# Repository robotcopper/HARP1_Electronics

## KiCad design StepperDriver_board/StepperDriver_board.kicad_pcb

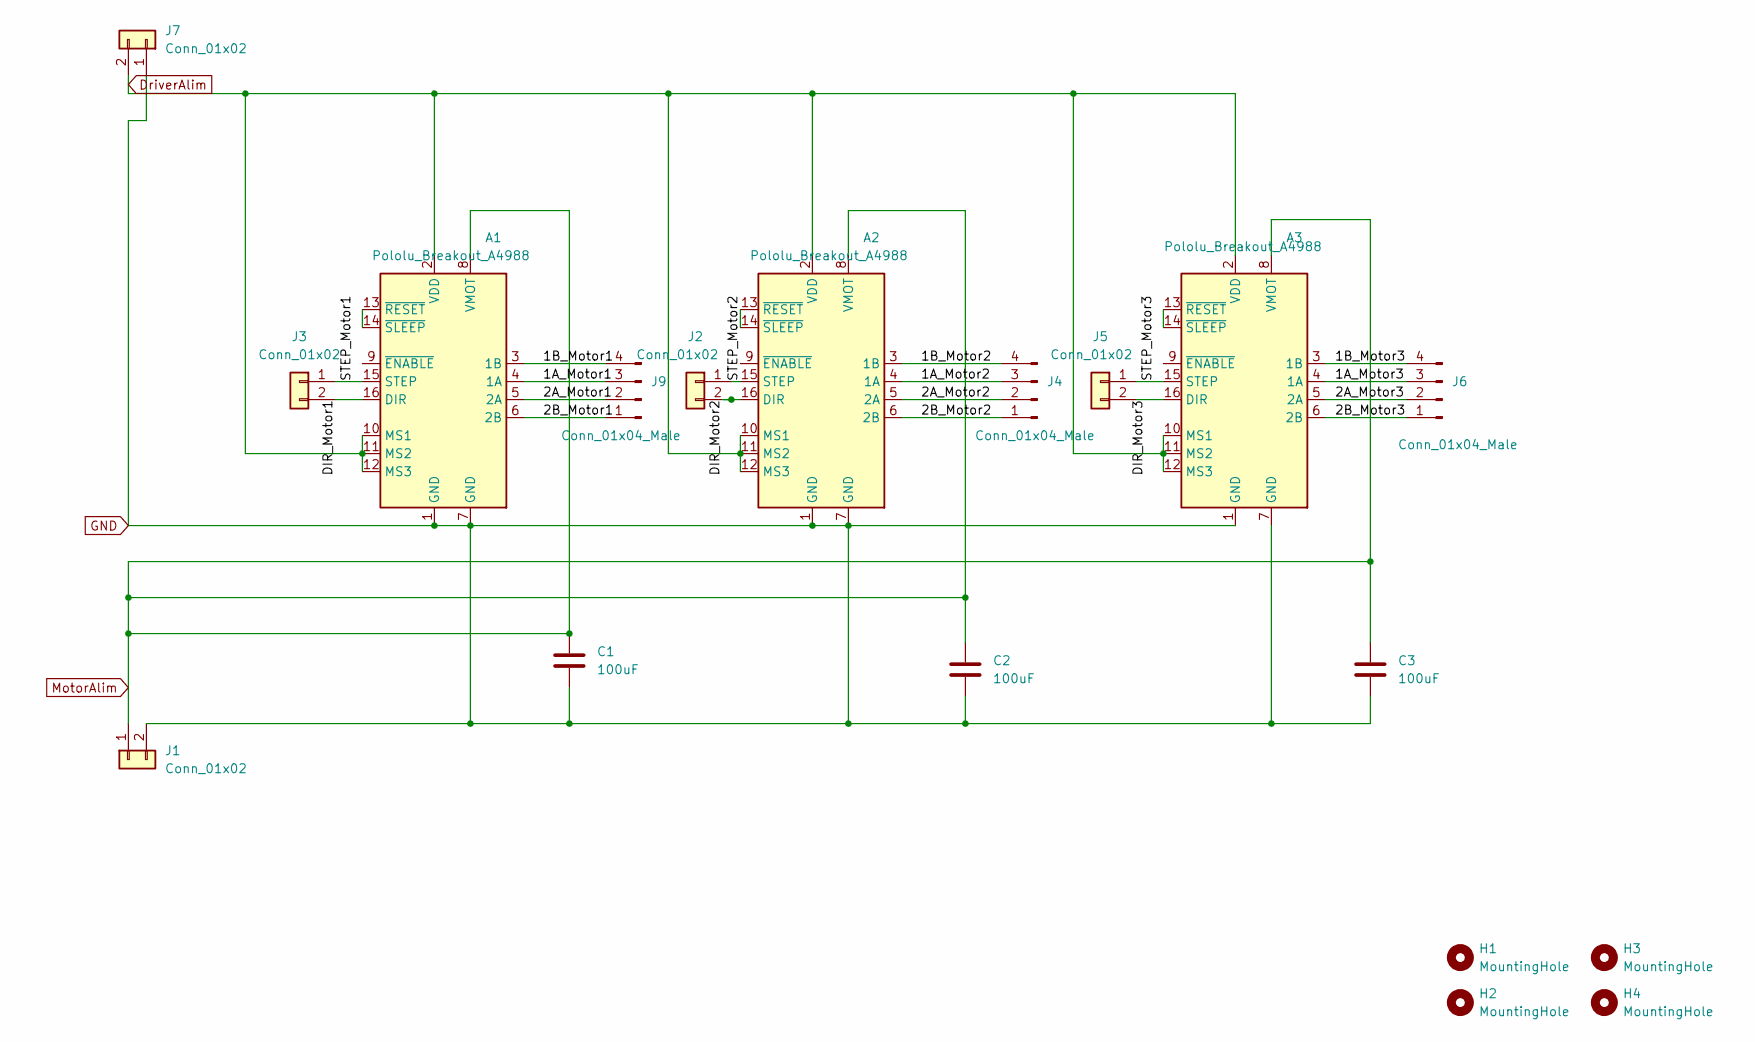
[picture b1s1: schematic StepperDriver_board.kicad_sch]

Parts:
A1, A2, A3: Pololu_Breakout_A4988; Pololu_Breakout-16_15.2x20.3mm
C1, C2, C3: 100uF; C_Radial_D8.0mm_H11.5mm_P3.50mm
H1, H2, H3, H4: MountingHole; MountingHole_3mm
J1, J2, J3, J5, J7: Conn_01x02; TerminalBlock_MetzConnect_Type073_RT02602HBLU_1x02_P5.08mm_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
J4, J6, J9: Conn_01x04_Male; PinHeader_1x04_P2.54mm_Vertical

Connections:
/1A_Motor1: A1.4 (1A), J9.3
/1A_Motor2: A2.4 (1A), J4.3
/1A_Motor3: A3.4 (1A), J6.3
/1B_Motor1: A1.3 (1B), J9.4
/1B_Motor2: A2.3 (1B), J4.4
/1B_Motor3: A3.3 (1B), J6.4
/2A_Motor1: A1.5 (2A), J9.2
/2A_Motor2: A2.5 (2A), J4.2
/2A_Motor3: A3.5 (2A), J6.2
/2B_Motor1: A1.6 (2B), J9.1
/2B_Motor2: A2.6 (2B), J4.1
/2B_Motor3: A3.6 (2B), J6.1
/DIR_Motor1: A1.16 (DIR), J3.2
/DIR_Motor2: A2.16 (DIR), J2.2
/DIR_Motor3: A3.16 (DIR), J5.2
/STEP_Motor1: A1.15 (STEP), J3.1
/STEP_Motor2: A2.15 (STEP), J2.1
/STEP_Motor3: A3.15 (STEP), J5.1
DriverAlim: A1.2 (VDD), A1.10 (MS1), A1.11 (MS2), A1.12 (MS3), A2.2 (VDD), A2.10 (MS1), A2.11 (MS2), A2.12 (MS3), A3.2 (VDD), A3.10 (MS1), A3.11 (MS2), A3.12 (MS3), J7.2
GND: A1.1 (GND), A1.7 (GND), A2.1 (GND), A2.7 (GND), A3.1 (GND), A3.7 (GND), C1.2, C2.2, C3.2, J1.2, J7.1
MotorAlim: A1.8 (VMOT), A2.8 (VMOT), A3.8 (VMOT), C1.1, C2.1, C3.1, J1.1
unnamed: A1.13 (~RESET), A1.14 (~SLEEP)
unnamed: A2.13 (~RESET), A2.14 (~SLEEP)
unnamed: A3.13 (~RESET), A3.14 (~SLEEP)

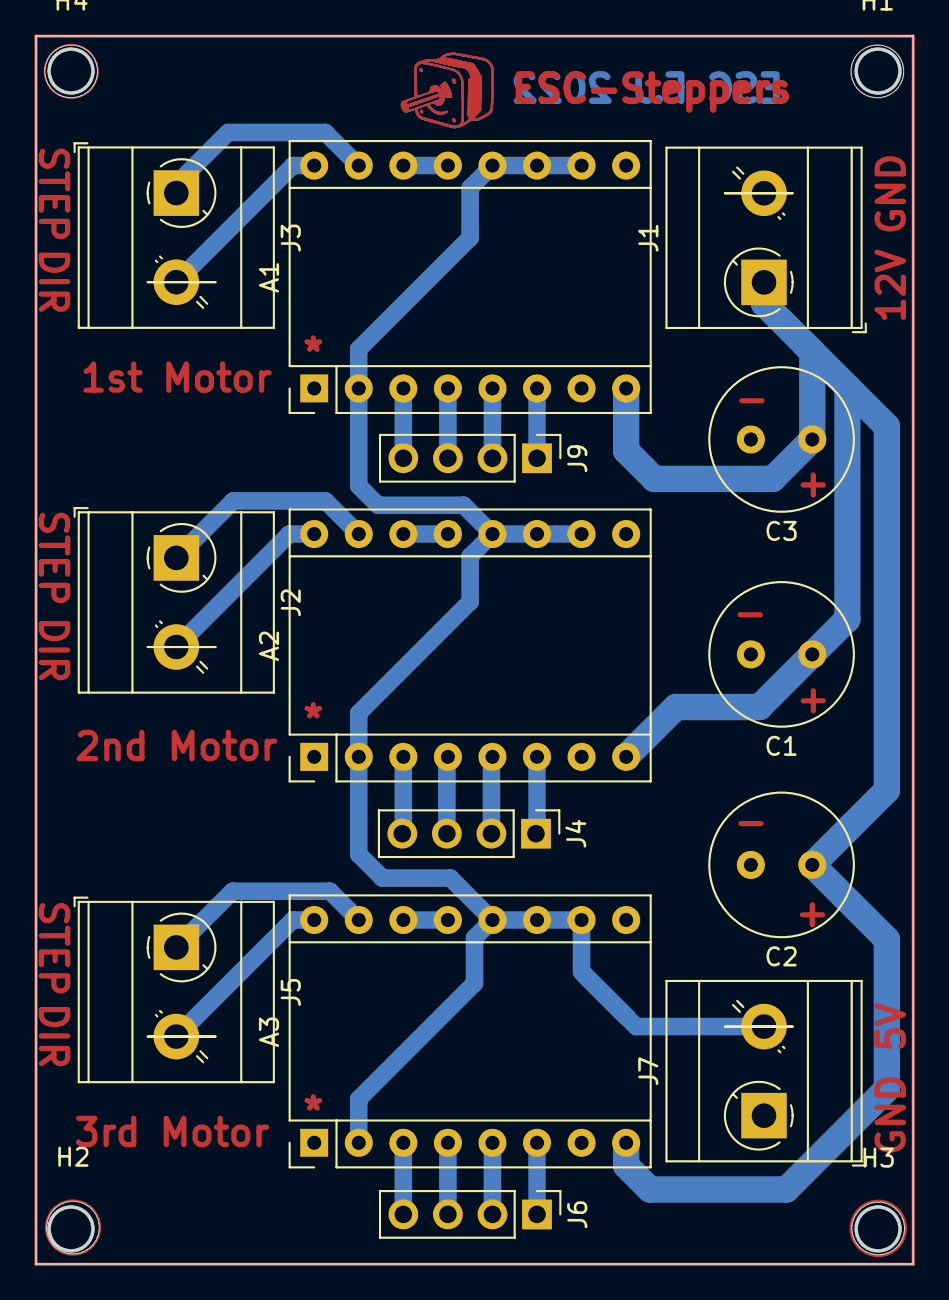
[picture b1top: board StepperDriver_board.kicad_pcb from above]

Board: 2 copper layers, 49.9 x 69.9 mm, 18 parts (0 on the bottom side), 24 nets.

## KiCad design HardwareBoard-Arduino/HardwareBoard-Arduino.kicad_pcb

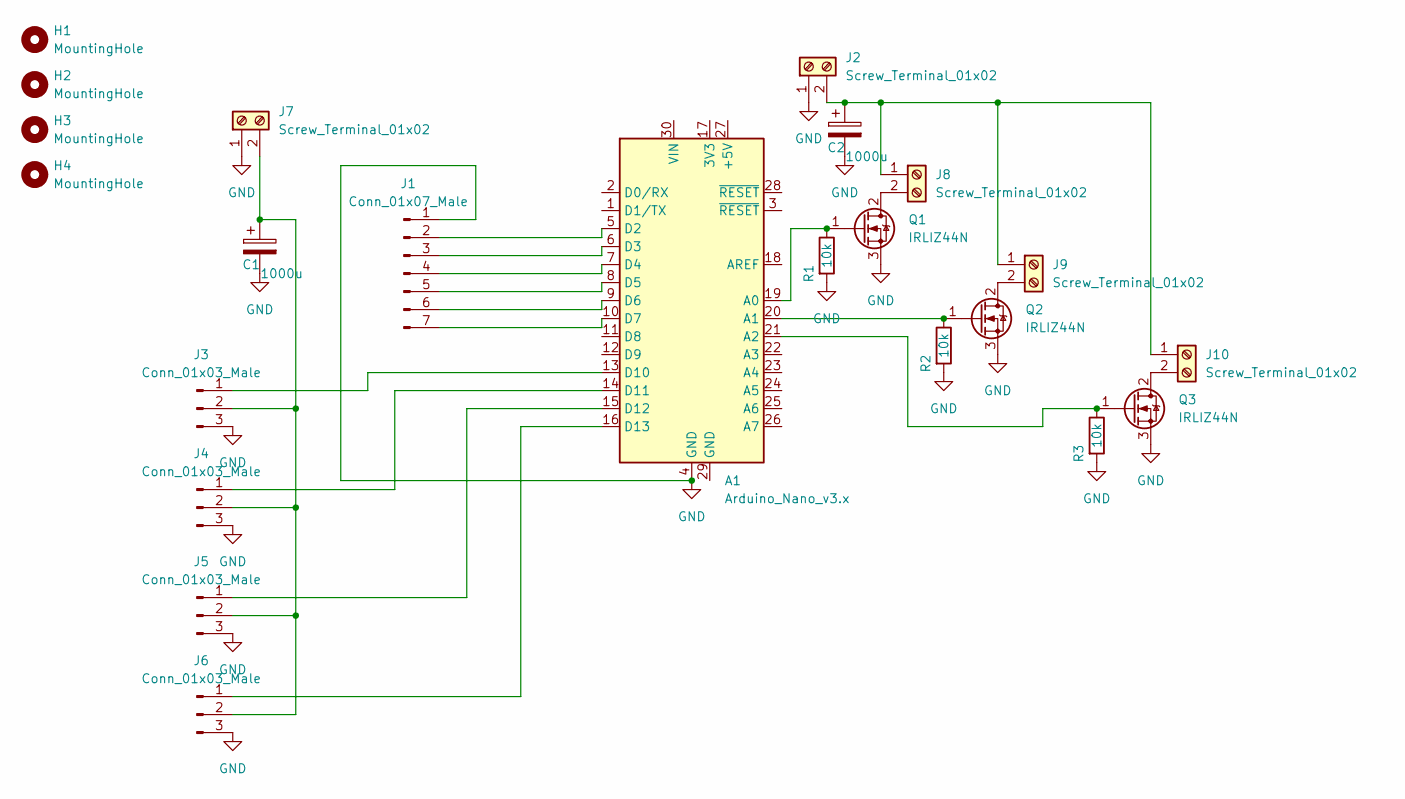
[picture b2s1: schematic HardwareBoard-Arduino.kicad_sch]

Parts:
A1: Arduino_Nano_v3.x; Arduino_Nano
C1, C2: 1000u; CP_Radial_D8.0mm_P3.80mm
H1, H2, H3, H4: MountingHole; MountingHole_3mm
J1: Conn_01x07_Male; PinHeader_1x07_P2.00mm_Vertical
J2, J7, J8, J9, J10: Screw_Terminal_01x02; TerminalBlock_Phoenix_MKDS-1,5-2_1x02_P5.00mm_Horizontal
J3, J4, J5, J6: Conn_01x03_Male; PinHeader_1x03_P2.00mm_Vertical
Q1, Q2, Q3: IRLIZ44N; TO-220F-3_Vertical
R1, R2, R3: 10k; R_Axial_DIN0207_L6.3mm_D2.5mm_P10.16mm_Horizontal

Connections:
GND: A1.4 (GND), C1.2, C2.2, J1.1, J2.1, J3.3, J4.3, J5.3, J6.3, J7.1, Q1.3 (S), Q2.3 (S), Q3.3 (S), R1.2, R2.2, R3.2
unnamed: A1.5 (D2), J1.2
unnamed: A1.6 (D3), J1.3
unnamed: A1.7 (D4), J1.4
unnamed: A1.8 (D5), J1.5
unnamed: A1.9 (D6), J1.6
unnamed: A1.10 (D7), J1.7
unnamed: A1.13 (D10), J3.1
unnamed: A1.14 (D11), J4.1
unnamed: A1.15 (D12), J5.1
unnamed: A1.16 (D13), J6.1
unnamed: A1.19 (A0), Q1.1 (G), R1.1
unnamed: A1.20 (A1), Q2.1 (G), R2.1
unnamed: A1.21 (A2), Q3.1 (G), R3.1
unnamed: C1.1, J3.2, J4.2, J5.2, J6.2, J7.2
unnamed: J8.2, Q1.2 (D)
unnamed: J9.2, Q2.2 (D)
unnamed: C2.1, J2.2, J8.1, J9.1, J10.1
unnamed: J10.2, Q3.2 (D)

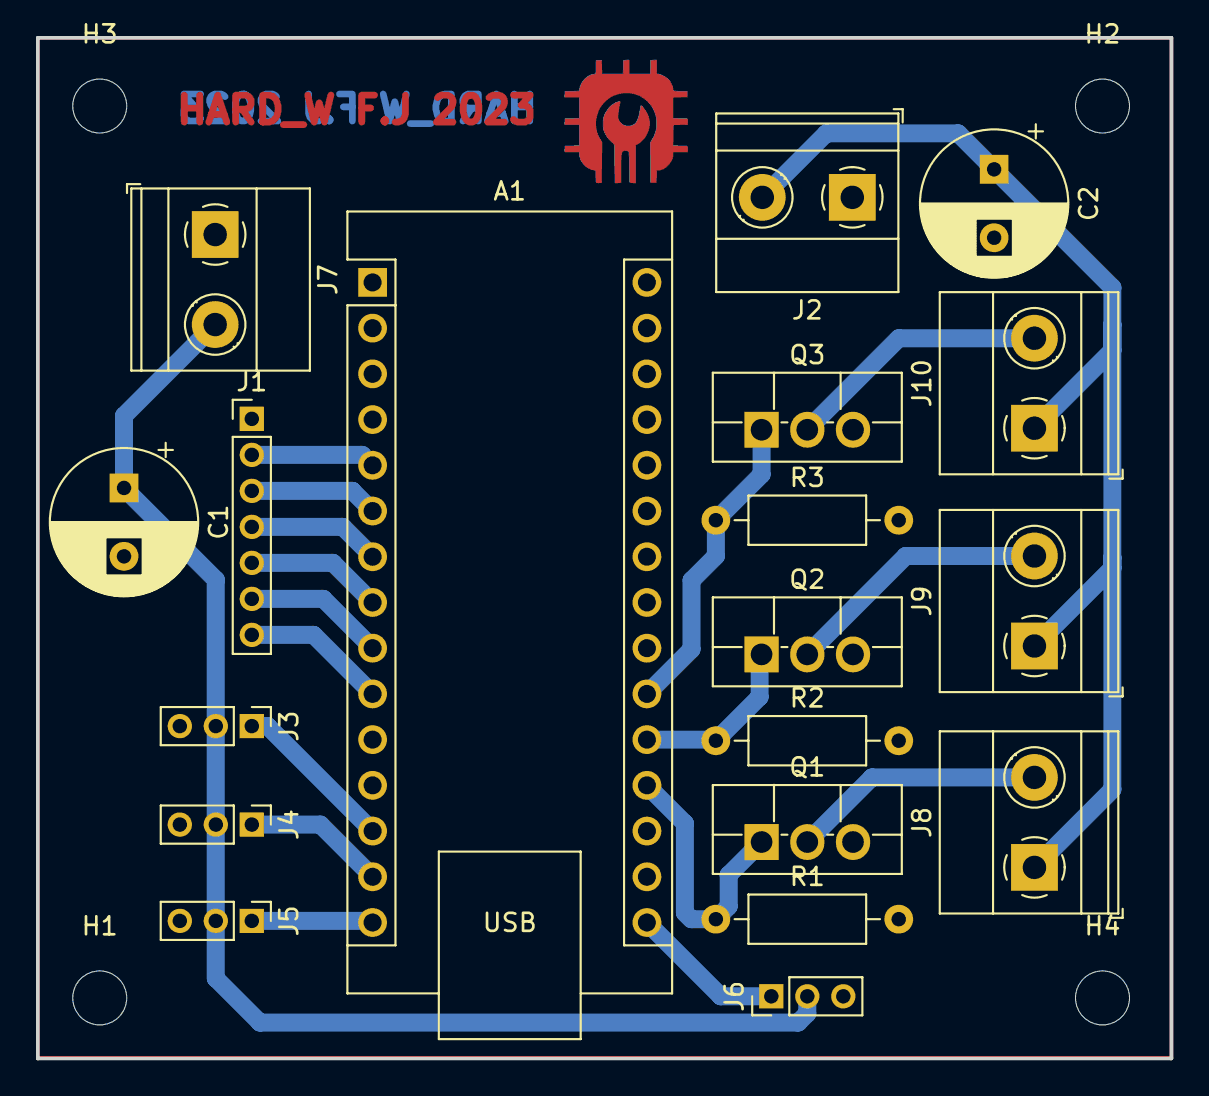
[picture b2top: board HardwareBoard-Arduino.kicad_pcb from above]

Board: 2 copper layers, 63.0 x 56.7 mm, 23 parts (0 on the bottom side), 19 nets.

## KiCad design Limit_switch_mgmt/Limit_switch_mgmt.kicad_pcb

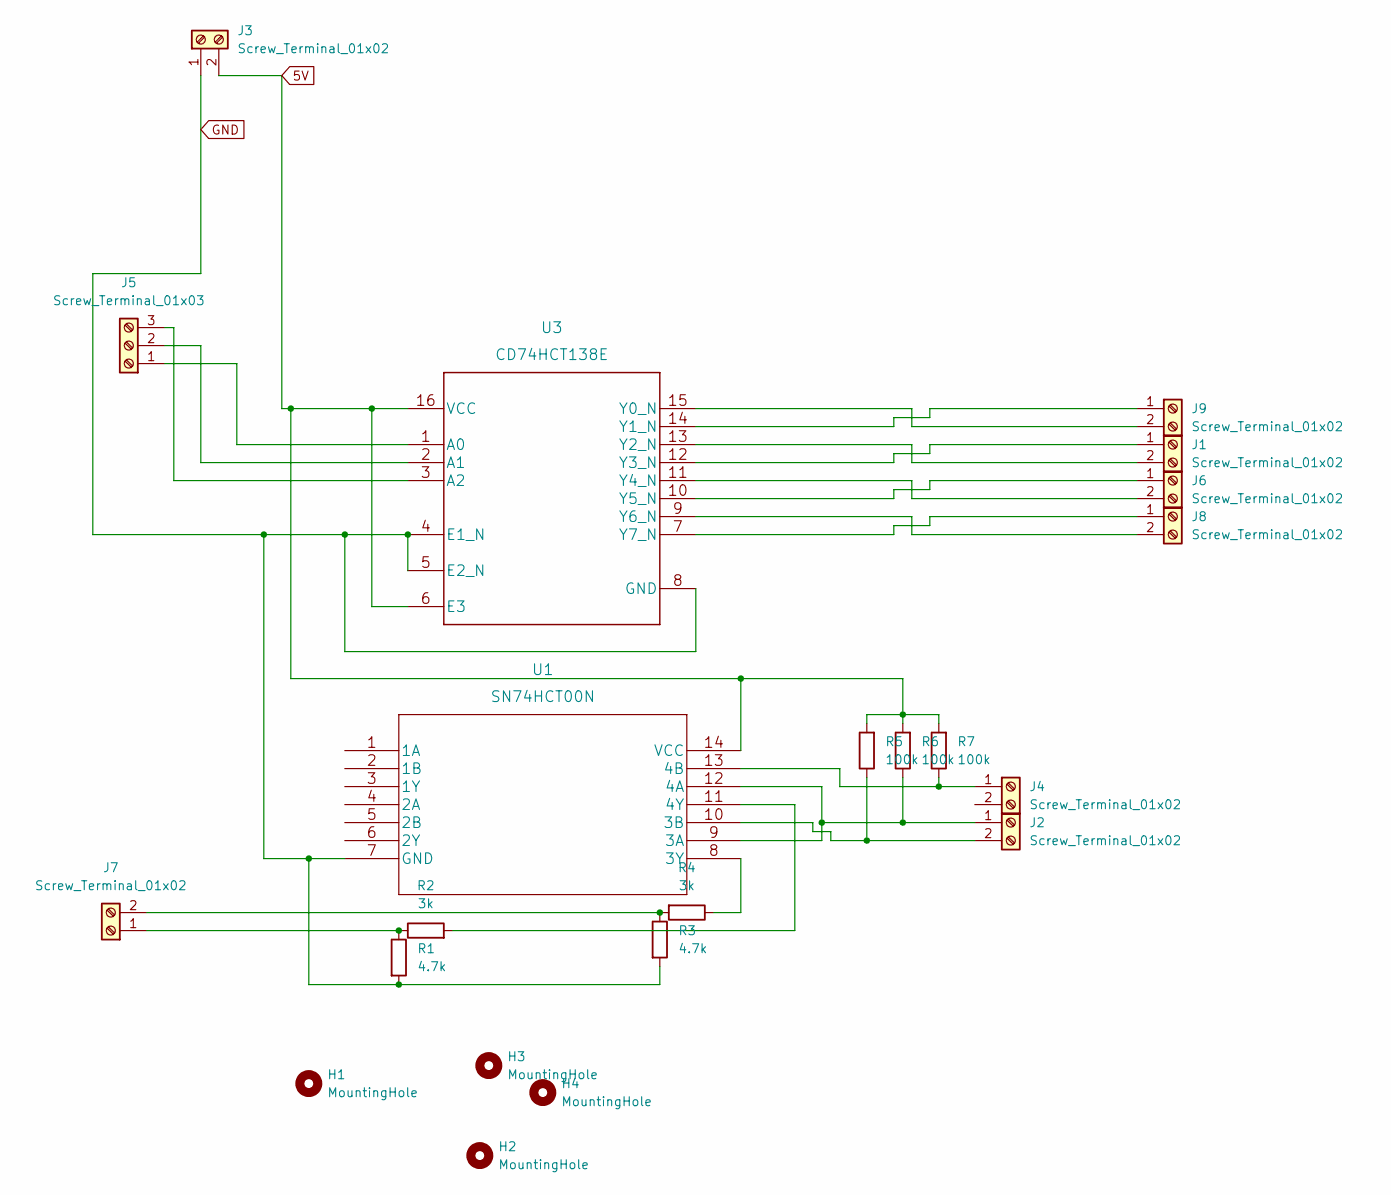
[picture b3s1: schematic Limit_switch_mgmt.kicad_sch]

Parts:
H1: MountingHole
H2, H3, H4: MountingHole; MountingHole_3mm
J1, J2, J3, J4, J6, J7, J8, J9: Screw_Terminal_01x02; TerminalBlock_MetzConnect_Type073_RT02602HBLU_1x02_P5.08mm_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
J5: Screw_Terminal_01x03; TerminalBlock_Phoenix_MKDS-3-3-5.08_1x03_P5.08mm_Horizontal
R1, R3: 4.7k; R_Axial_DIN0207_L6.3mm_D2.5mm_P10.16mm_Horizontal
R2, R4: 3k; R_Axial_DIN0207_L6.3mm_D2.5mm_P10.16mm_Horizontal
R5, R6, R7: 100k; R_Axial_DIN0207_L6.3mm_D2.5mm_P10.16mm_Horizontal
U1: SN74HCT00N
U3: CD74HCT138E

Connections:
5V: J3.2, R5.2, R6.2, R7.2, U1.14 (VCC), U3.6 (E3), U3.16 (VCC)
GND: J3.1, R1.2, R3.2, U1.7 (GND), U3.4 (E1_N), U3.5 (E2_N), U3.8 (GND)
unnamed: J1.1, U3.12 (Y3_N)
unnamed: J1.2, U3.13 (Y2_N)
unnamed: J2.1, R6.1, U1.9 (3A), U1.12 (4A)
unnamed: J2.2, R5.1, U1.10 (3B)
unnamed: J4.1, R7.1, U1.13 (4B)
unnamed: J5.1, U3.1 (A0)
unnamed: J5.2, U3.2 (A1)
unnamed: J5.3, U3.3 (A2)
unnamed: J6.1, U3.10 (Y5_N)
unnamed: J6.2, U3.11 (Y4_N)
unnamed: J7.1, R1.1, R2.1
unnamed: J7.2, R3.1, R4.2
unnamed: J8.1, U3.7 (Y7_N)
unnamed: J8.2, U3.9 (Y6_N)
unnamed: J9.1, U3.14 (Y1_N)
unnamed: J9.2, U3.15 (Y0_N)
unnamed: R2.2, U1.11 (4Y)
unnamed: R4.1, U1.8 (3Y)

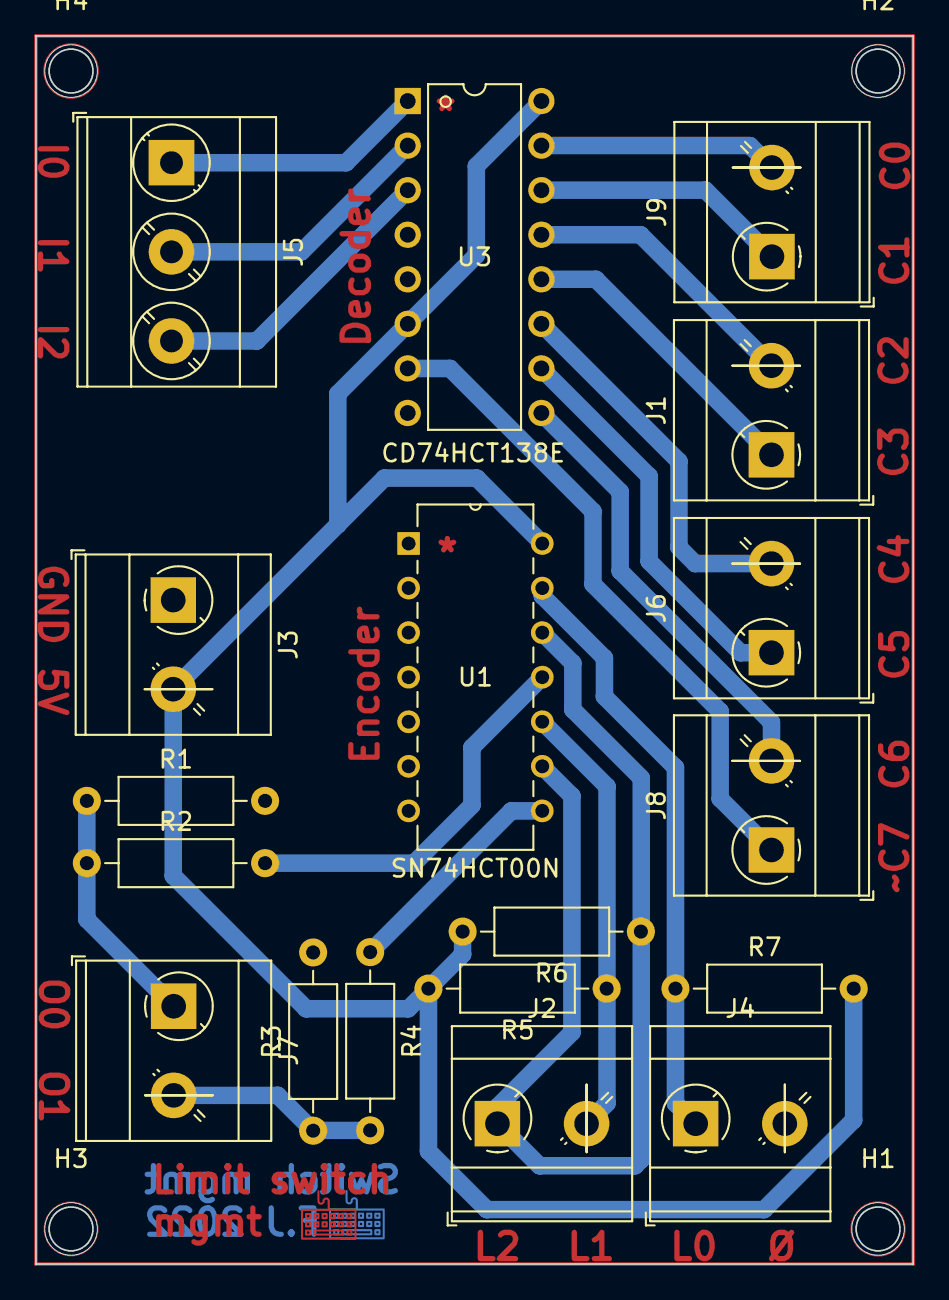
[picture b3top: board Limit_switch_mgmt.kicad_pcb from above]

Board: 2 copper layers, 50.0 x 70.0 mm, 22 parts (0 on the bottom side), 20 nets.

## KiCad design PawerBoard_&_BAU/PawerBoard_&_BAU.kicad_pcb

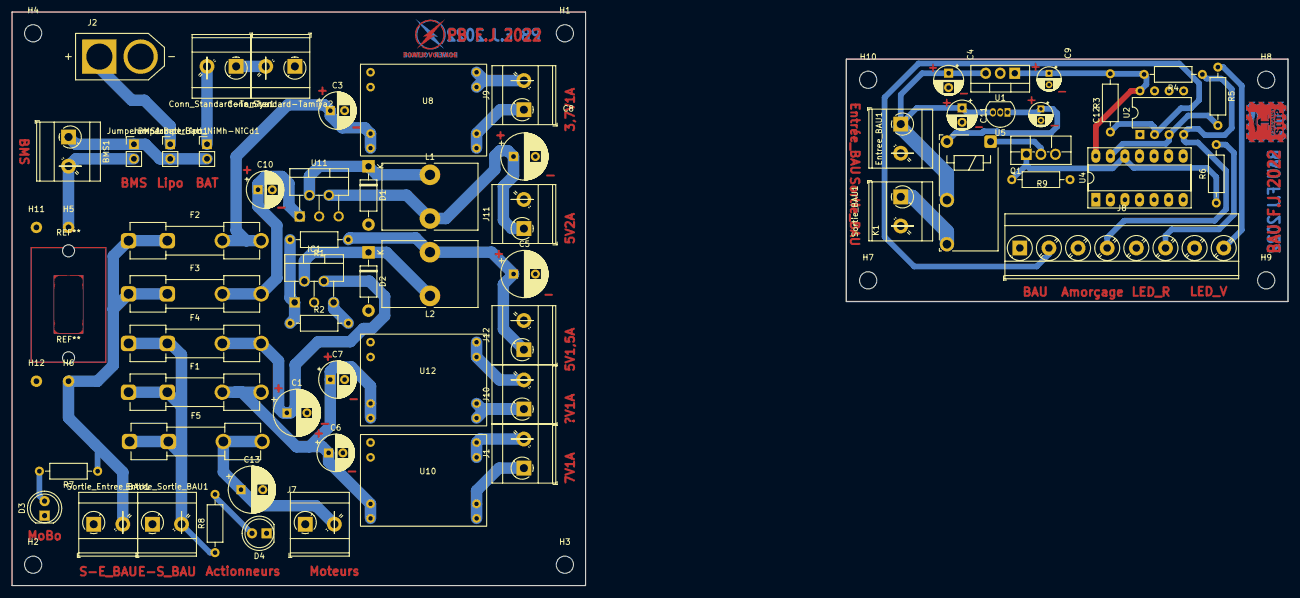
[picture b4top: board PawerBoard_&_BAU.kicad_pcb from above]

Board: 2 copper layers, 222.5 x 100.0 mm, 73 parts (0 on the bottom side), 39 nets.

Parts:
BMS1: Conn_01x02; TerminalBlock_MetzConnect_Type073_RT02602HBLU_1x02_P5.08mm_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
C1: 330u; CP_Radial_D8.0mm_P3.50mm
C3, C6, C7, C10: 100u; CP_Radial_D6.3mm_P2.50mm
C4, C11: 0,47u; CP_Radial_D5.0mm_P2.50mm
C5, C8, C13: 1000u; CP_Radial_D8.0mm_P3.80mm
C9, C12: 0,1u; CP_Radial_D4.0mm_P2.00mm
Conn_Standard-Tamiya1, Conn_Standard-Tamiya2: Conn_01x02; TerminalBlock_MetzConnect_Type073_RT02602HBLU_1x02_P5.08mm_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
D1, D2: 1N5819; D_DO-41_SOD81_P10.16mm_Horizontal
D3, D4: LED; LED_D5.0mm
Entree_BAU1: Conn_01x02; TerminalBlock_MetzConnect_Type073_RT02602HBLU_1x02_P5.08mm_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
Entree_Sortie_BAU1: Conn_01x02; TerminalBlock_MetzConnect_Type073_RT02602HBLU_1x02_P5.08mm_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
F1, F2: 1A; Fuseholder_Clip-5x20mm_Keystone_3517_Inline_P23.11x6.76mm_D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
F3: 2.5A; Fuseholder_Clip-5x20mm_Keystone_3517_Inline_P23.11x6.76mm_D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
F4: 1,5A; Fuseholder_Clip-5x20mm_Keystone_3517_Inline_P23.11x6.76mm_D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
F5: 4A; Fuseholder_Clip-5x20mm_Keystone_3517_Inline_P23.11x6.76mm_D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
H1, H2, H3, H4, H7, H8, H9, H10: MountingHole; MountingHole_3mm
H5, H6, H11, H12: MountingHole_Pad; MountingHole_2.2mm_M2_Pad
IC1: MC34167TG; TO-220-5_P3.4x3.7mm_StaggerOdd_Lead3.8mm_Vertical
J1, J7, J9, J10, J11, J12: Conn_01x02; TerminalBlock_MetzConnect_Type073_RT02602HBLU_1x02_P5.08mm_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
J2: XT60-M; AMASS_XT60-M
J8: Screw_Terminal_01x08; TerminalBlock_Phoenix_MKDS-3-8-5.08_1x08_P5.08mm_Horizontal
JumperBMS1: Conn_01x02_Male; PinHeader_1x02_P2.54mm_Vertical
JumperBatt_Lipo1: Conn_01x02_Male; PinHeader_1x02_P2.54mm_Vertical
JumperBatt_NiMh-NiCd1: Conn_01x02_Male; PinHeader_1x02_P2.54mm_Vertical
K1: TE_PCH-1xxx2M; Relay_SPST_TE_PCH-1xxx2M
L1, L2: 100u; L_Toroid_Vertical_L16.5mm_W11.4mm_P7.62mm_Pulse_KM-2
Q1: IRLIZ44N; TO-220F-3_Vertical
R1: 6.8k; R_Axial_DIN0207_L6.3mm_D2.5mm_P10.16mm_Horizontal
R2: 68k; R_Axial_DIN0207_L6.3mm_D2.5mm_P10.16mm_Horizontal
R3, R4, R9: 10k; R_Axial_DIN0207_L6.3mm_D2.5mm_P10.16mm_Horizontal
R5, R6: 220; R_Axial_DIN0207_L6.3mm_D2.5mm_P10.16mm_Horizontal
R7, R8: 500k; R_Axial_DIN0207_L6.3mm_D2.5mm_P10.16mm_Horizontal
Sortie_BAU1: Conn_01x02; TerminalBlock_MetzConnect_Type073_RT02602HBLU_1x02_P5.08mm_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
Sortie_Entree_BAU1: Conn_01x02; TerminalBlock_MetzConnect_Type073_RT02602HBLU_1x02_P5.08mm_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
U1: L78L05_TO92; TO-220-3_Vertical
U2: NE555P; DIP-8_W7.62mm
U4: 74LS04; DIP-14_W7.62mm_Socket_LongPads
U5: L78L12_TO92; TO-92_Inline
U8, U10, U12: LM2596-Dsun
U11: LM2576T-5; TO-220-5_P3.4x3.7mm_StaggerOdd_Lead3.8mm_Vertical

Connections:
3,7V3A: J9.1, U8.4 (OUT)
5V1,5A: C5.1, J12.1, L2.2, R1.1
5V3A: C8.1, J11.1, L1.2, U11.4 (FB)
7V3A: J1.1, U10.4 (OUT)
?V3A: J10.1, U12.4 (OUT)
Amorçage: J8.4, R4.1, U2.4 (R)
BAU: J8.2, R3.1, U2.2 (TR)
GND: C1.2, C3.2, C5.2, C6.2, C7.2, C8.2, C10.2, C13.2, Conn_Standard-Tamiya2.1, D1.2 (A), D2.2 (A), D3.1 (K), D4.1 (K), Entree_Sortie_BAU1.1, IC1.3 (GROUND), J2.N (NEG), J7.1, J11.2, J12.2, Sortie_Entree_BAU1.1, U8.1 (GND_IN), U10.1 (GND_IN), U11.3 (GND), U11.5 (~ON/OFF), U12.1 (GND_IN)
GND1: C4.2, C9.2, C11.2, C12.2, Entree_BAU1.2, J8.1, J8.3, J8.5, J8.7, Q1.3 (S), R9.2, Sortie_BAU1.2, U1.2 (GND), U2.1 (GND), U2.5 (CV), U2.6 (THR), U4.7 (GND), U5.2 (GND)
LED_Rouge: J8.6, R6.2
LED_Verte: J8.8, R5.1
unnamed: BMS1.1, JumperBMS1.1, JumperBatt_Lipo1.2, JumperBatt_NiMh-NiCd1.2
unnamed: BMS1.2, H5.1, JumperBMS1.2
unnamed: C1.1, F4.2, IC1.4 (INPUT_VOLTAGE/VCC)
unnamed: C3.1, F2.2, U8.2 (IN)
unnamed: C6.1, C7.1, F1.2, U10.2 (IN), U12.2 (IN)
unnamed: C9.1, R3.2, R4.2, U1.1 (VO), U2.8 (VCC), U4.14 (VCC)
unnamed: C10.1, F3.2, U11.1 (VIN)
unnamed: C4.1, C11.1, Entree_BAU1.1, K1.2, U1.3 (VI), U5.3 (VI)
unnamed: C12.1, K1.5, U5.1 (VO)
unnamed: C13.1, F5.2, J7.2
unnamed: Conn_Standard-Tamiya1.1, Conn_Standard-Tamiya2.2
unnamed: Conn_Standard-Tamiya1.2, JumperBatt_NiMh-NiCd1.1
unnamed: D1.1 (K), L1.1, U11.2 (OUT)
unnamed: D2.1 (K), IC1.2 (SWITCH_OUTPUT), L2.1
unnamed: D3.2 (A), R7.2
unnamed: D4.2 (A), R8.2
unnamed: Entree_Sortie_BAU1.2, F1.1, F4.1, F5.1, R8.1
unnamed: F2.1, F3.1, H6.1, R7.1, Sortie_Entree_BAU1.2
unnamed: IC1.1 (VOLTAGE_FEEDBACK_INPUT), R1.2, R2.1
unnamed: IC1.5 (_COMPENSATION/STANDBY), R2.2
unnamed: J1.2, U10.3 (GND_OUT)
unnamed: J2.P (POS), JumperBatt_Lipo1.1
unnamed: J9.2, U8.3 (GND_OUT)
unnamed: J10.2, U12.3 (GND_OUT)
unnamed: K1.1, Q1.2 (D)
unnamed: Q1.1 (G), R6.1, R9.1, U4.12
unnamed: R5.2, U2.3 (Q), U4.13
unnamed: K1.3, Sortie_BAU1.1

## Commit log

2024-12-04 Feat: add HARP1 Kicad projects
2024-12-04 Feat: add assets
